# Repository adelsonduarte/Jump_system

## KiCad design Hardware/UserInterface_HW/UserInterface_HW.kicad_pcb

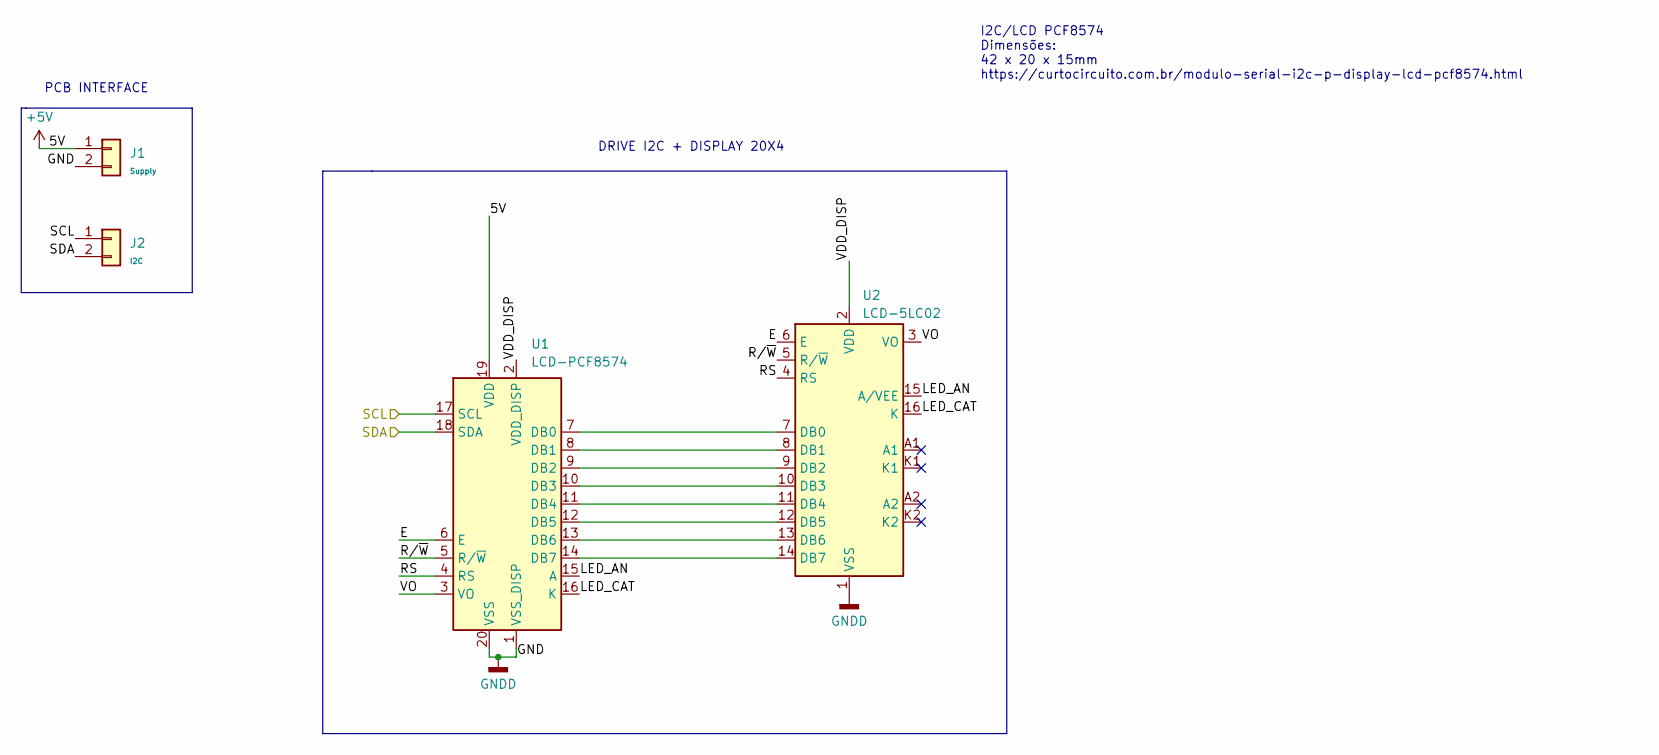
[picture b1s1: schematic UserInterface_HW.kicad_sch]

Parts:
J1: Supply; PinHeader_1x02_P2.54mm_Vertical
J2: I2C; PinHeader_1x02_P2.54mm_Vertical
U1: LCD-PCF8574; Módulo I2C - PCF8574
U2: LCD-5LC02; PinHeader_1x16_P2.54mm_Vertical

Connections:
+5V: J1.1, U1.19 (VDD)
/E: U1.6 (E), U2.6 (E)
/LED_AN: U1.15 (A), U2.15 (A/VEE)
/LED_CAT: U1.16 (K), U2.16 (K)
/RS: U1.4 (RS), U2.4 (RS)
/R/~W: U1.5 (R/~W), U2.5 (R/~W)
/SCL: J2.1, U1.17 (SCL)
/SDA: J2.2, U1.18 (SDA)
/VDD_DISP: U1.2 (VDD_DISP), U2.2 (VDD)
/VO: U1.3 (VO), U2.3 (VO)
GNDD: J1.2, U1.1 (VSS_DISP), U1.20 (VSS), U2.1 (VSS)
unnamed: U1.7 (DB0), U2.7 (DB0)
unnamed: U1.8 (DB1), U2.8 (DB1)
unnamed: U1.9 (DB2), U2.9 (DB2)
unnamed: U1.10 (DB3), U2.10 (DB3)
unnamed: U1.11 (DB4), U2.11 (DB4)
unnamed: U1.12 (DB5), U2.12 (DB5)
unnamed: U1.13 (DB6), U2.13 (DB6)
unnamed: U1.14 (DB7), U2.14 (DB7)

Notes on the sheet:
DRIVE I2C + DISPLAY 20X4
I2C/LCD PCF8574 Dimensões: 42 x 20 x 15mm https://curtocircuito.com.br/modulo-serial-i2c-p-display-lcd-pcf8574.html
PCB INTERFACE

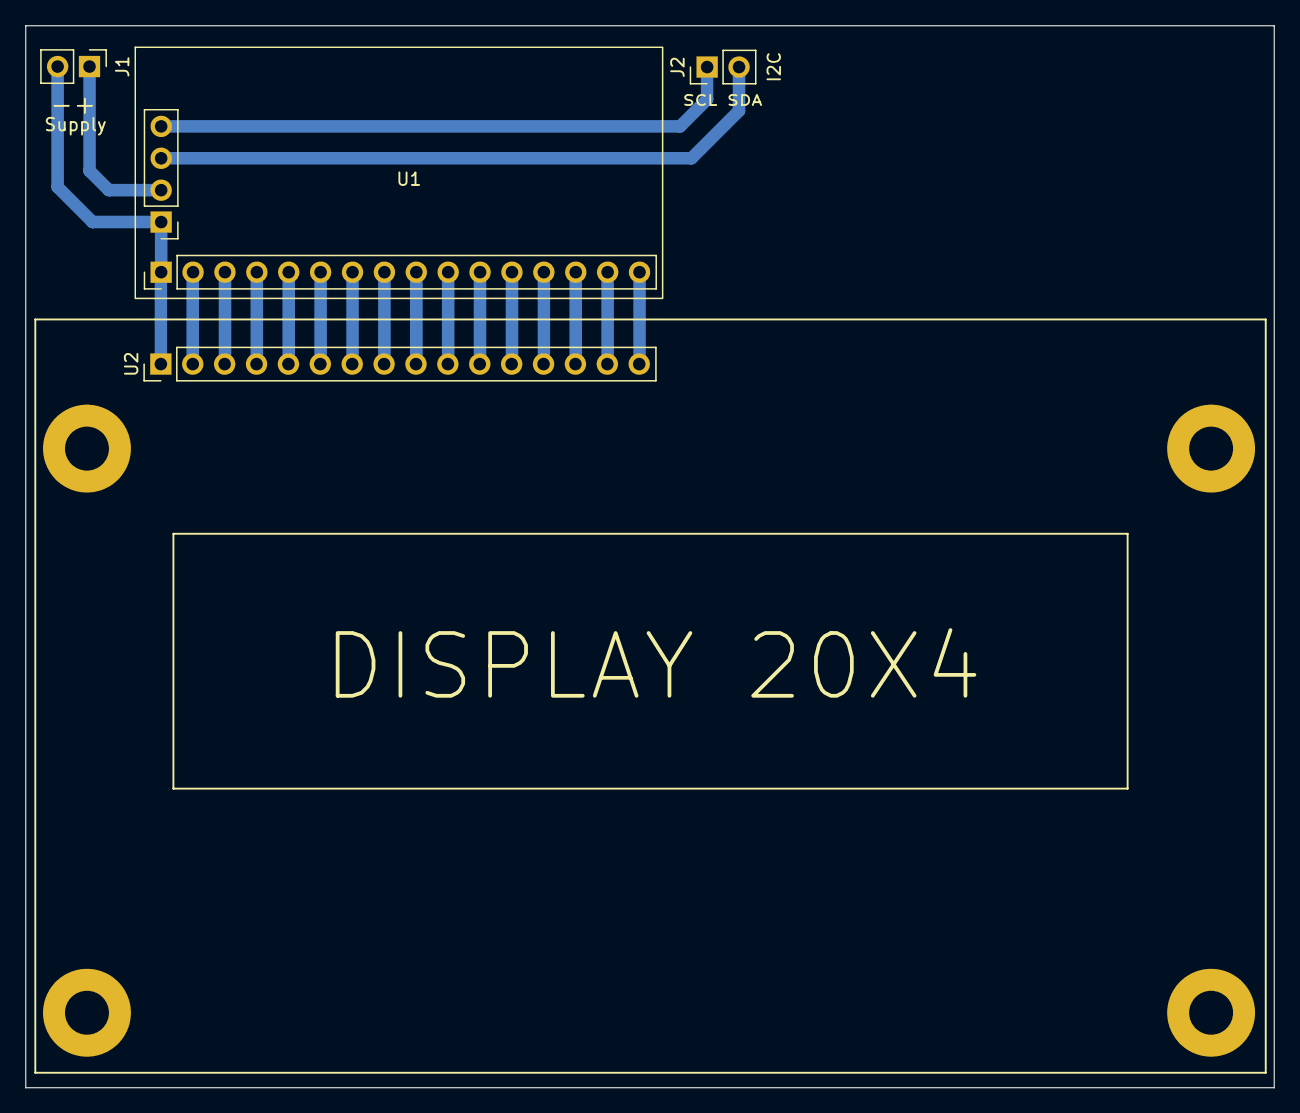
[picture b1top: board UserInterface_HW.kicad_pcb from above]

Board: 2 copper layers, 99.4 x 84.6 mm, 4 parts (0 on the bottom side), 19 nets.

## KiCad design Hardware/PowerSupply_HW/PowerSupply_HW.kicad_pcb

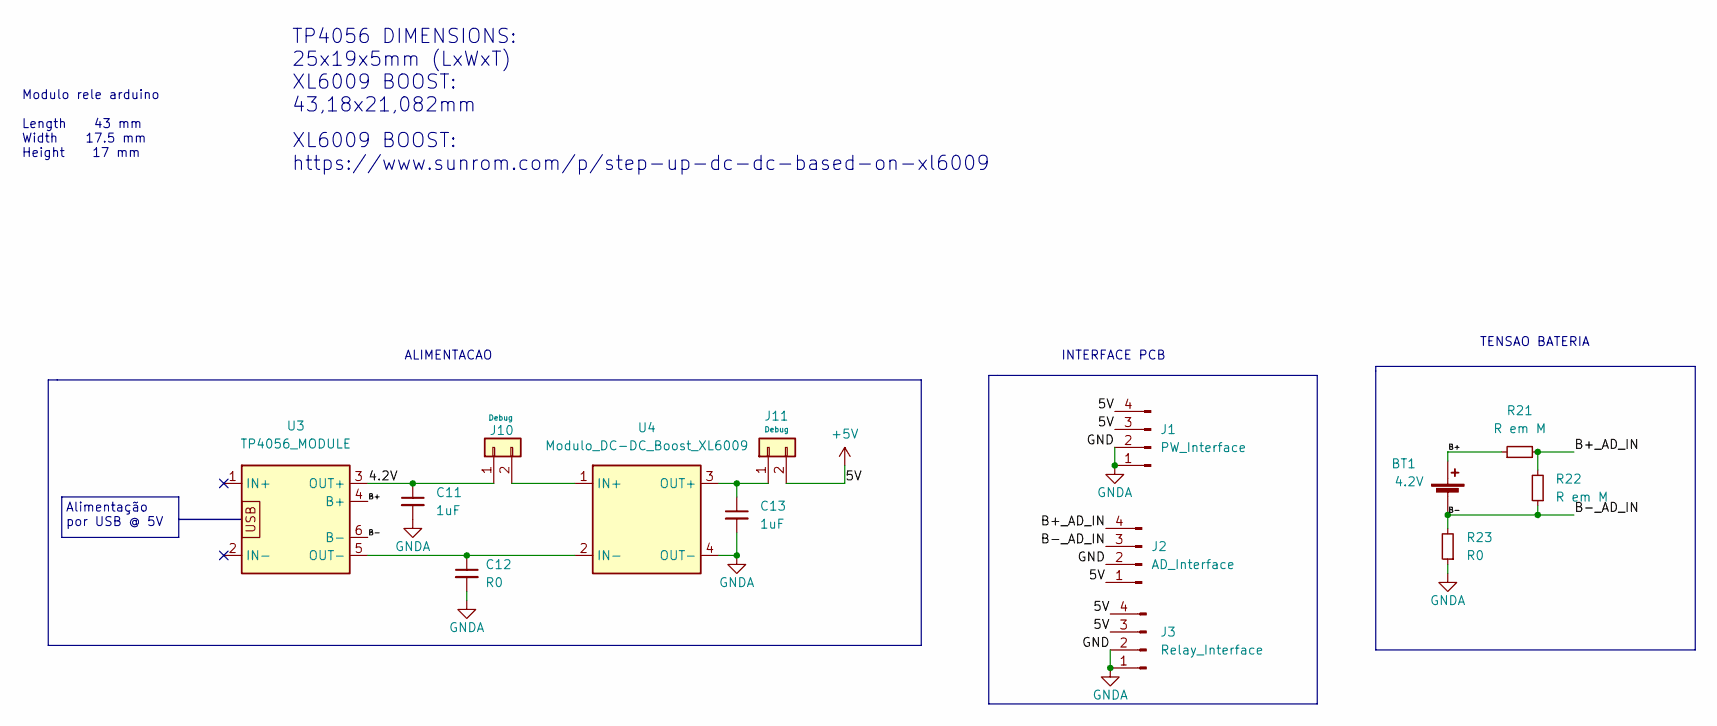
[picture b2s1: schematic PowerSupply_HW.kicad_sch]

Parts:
BT1: 4.2V; PinHeader_1x02_P2.54mm_Vertical
C11, C13: 1uF; C_0805_2012Metric
C12: R0; C_0805_2012Metric
J1: PW_Interface; PinHeader_1x04_P2.54mm_Vertical
J2: AD_Interface; PinHeader_1x04_P2.54mm_Vertical
J3: Relay_Interface; PinHeader_1x04_P2.54mm_Vertical
J10, J11: Debug; PinHeader_1x02_P2.54mm_Vertical
R21, R22: R em M; R_0805_2012Metric_Pad1.20x1.40mm_HandSolder
R23: R0; R_0805_2012Metric_Pad1.20x1.40mm_HandSolder
U3: TP4056_MODULE; Módulo_TP4056
U4: Modulo_DC-DC_Boost_XL6009

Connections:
+5V: J1.3, J1.4, J2.1, J3.3, J3.4, J11.2
/4.2V: C11.1, J10.1, U3.3 (OUT+)
/B+: BT1.1 (+), R21.1, U3.4 (B+); also elsewhere on the board
/B+_AD_IN: J2.4, R21.2, R22.2
/B-: BT1.2 (-), J2.3, R22.1, R23.2, U3.6 (B-); also elsewhere on the board
GNDA: C11.2, C12.2, C13.2, J1.1, J1.2, J2.2, J3.1, J3.2, R23.1, U4.4 (OUT-)
unnamed: C12.1, U3.5 (OUT-), U4.2 (IN-)
unnamed: C13.1, J11.1, U4.3 (OUT+)
unnamed: J10.2, U4.1 (IN+)

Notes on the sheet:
XL6009 BOOST: https://www.sunrom.com/p/step-up-dc-dc-based-on-xl6009
TENSAO BATERIA
Modulo rele arduino Length 43 mm Width 17.5 mm Height 17 mm
INTERFACE PCB
Alimentação por USB @ 5V
TP4056 DIMENSIONS: 25x19x5mm (LxWxT) XL6009 BOOST: 43,18x21,082mm
ALIMENTACAO

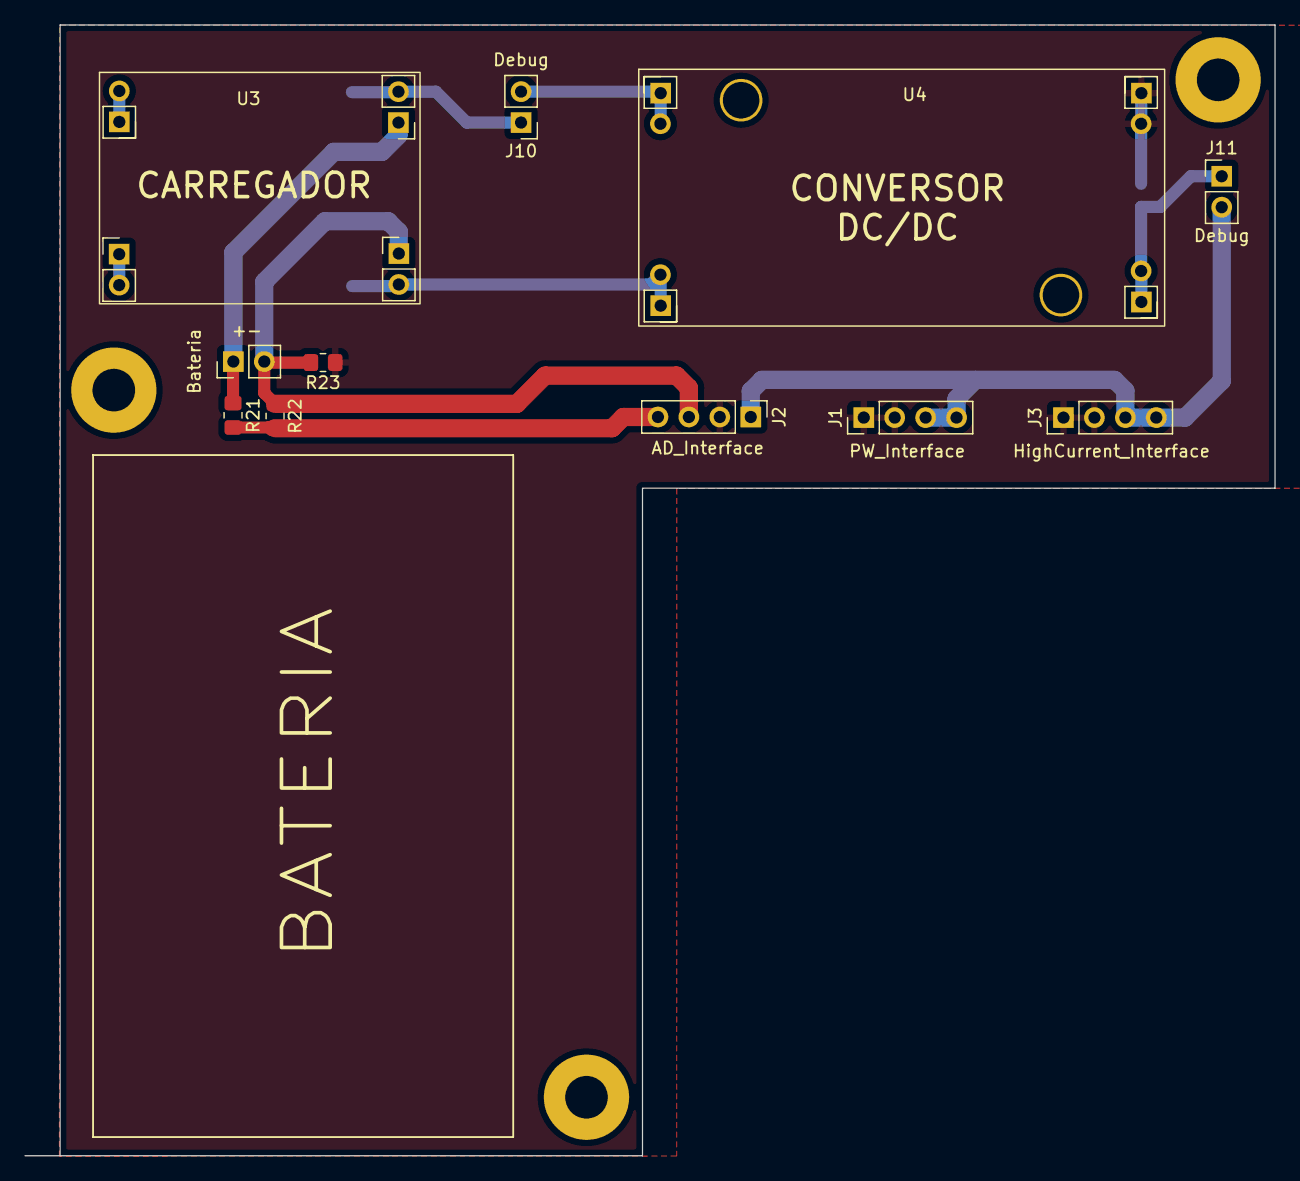
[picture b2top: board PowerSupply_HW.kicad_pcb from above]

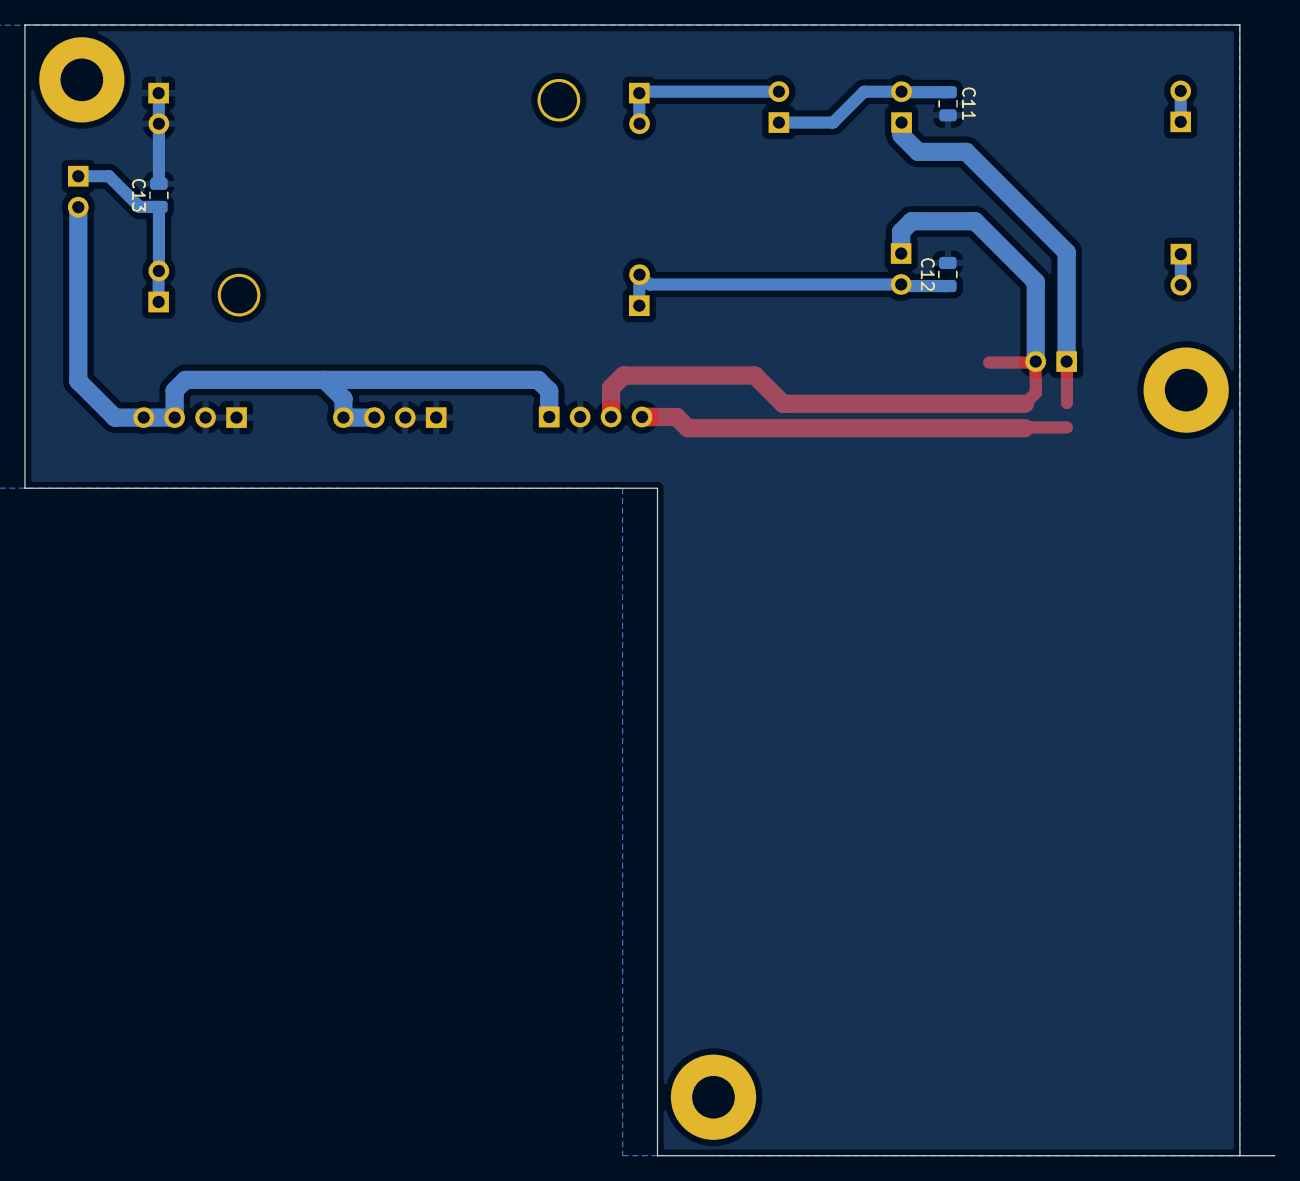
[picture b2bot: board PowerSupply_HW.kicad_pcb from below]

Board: 2 copper layers, 102.6 x 92.9 mm, 14 parts (3 on the bottom side), 9 nets.

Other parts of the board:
Bateria: 4.2V; PinHeader_1x02_P2.54mm_Vertical

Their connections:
/B+: Bateria.1 (+); also elsewhere on the board
/B-: Bateria.2 (-); also elsewhere on the board

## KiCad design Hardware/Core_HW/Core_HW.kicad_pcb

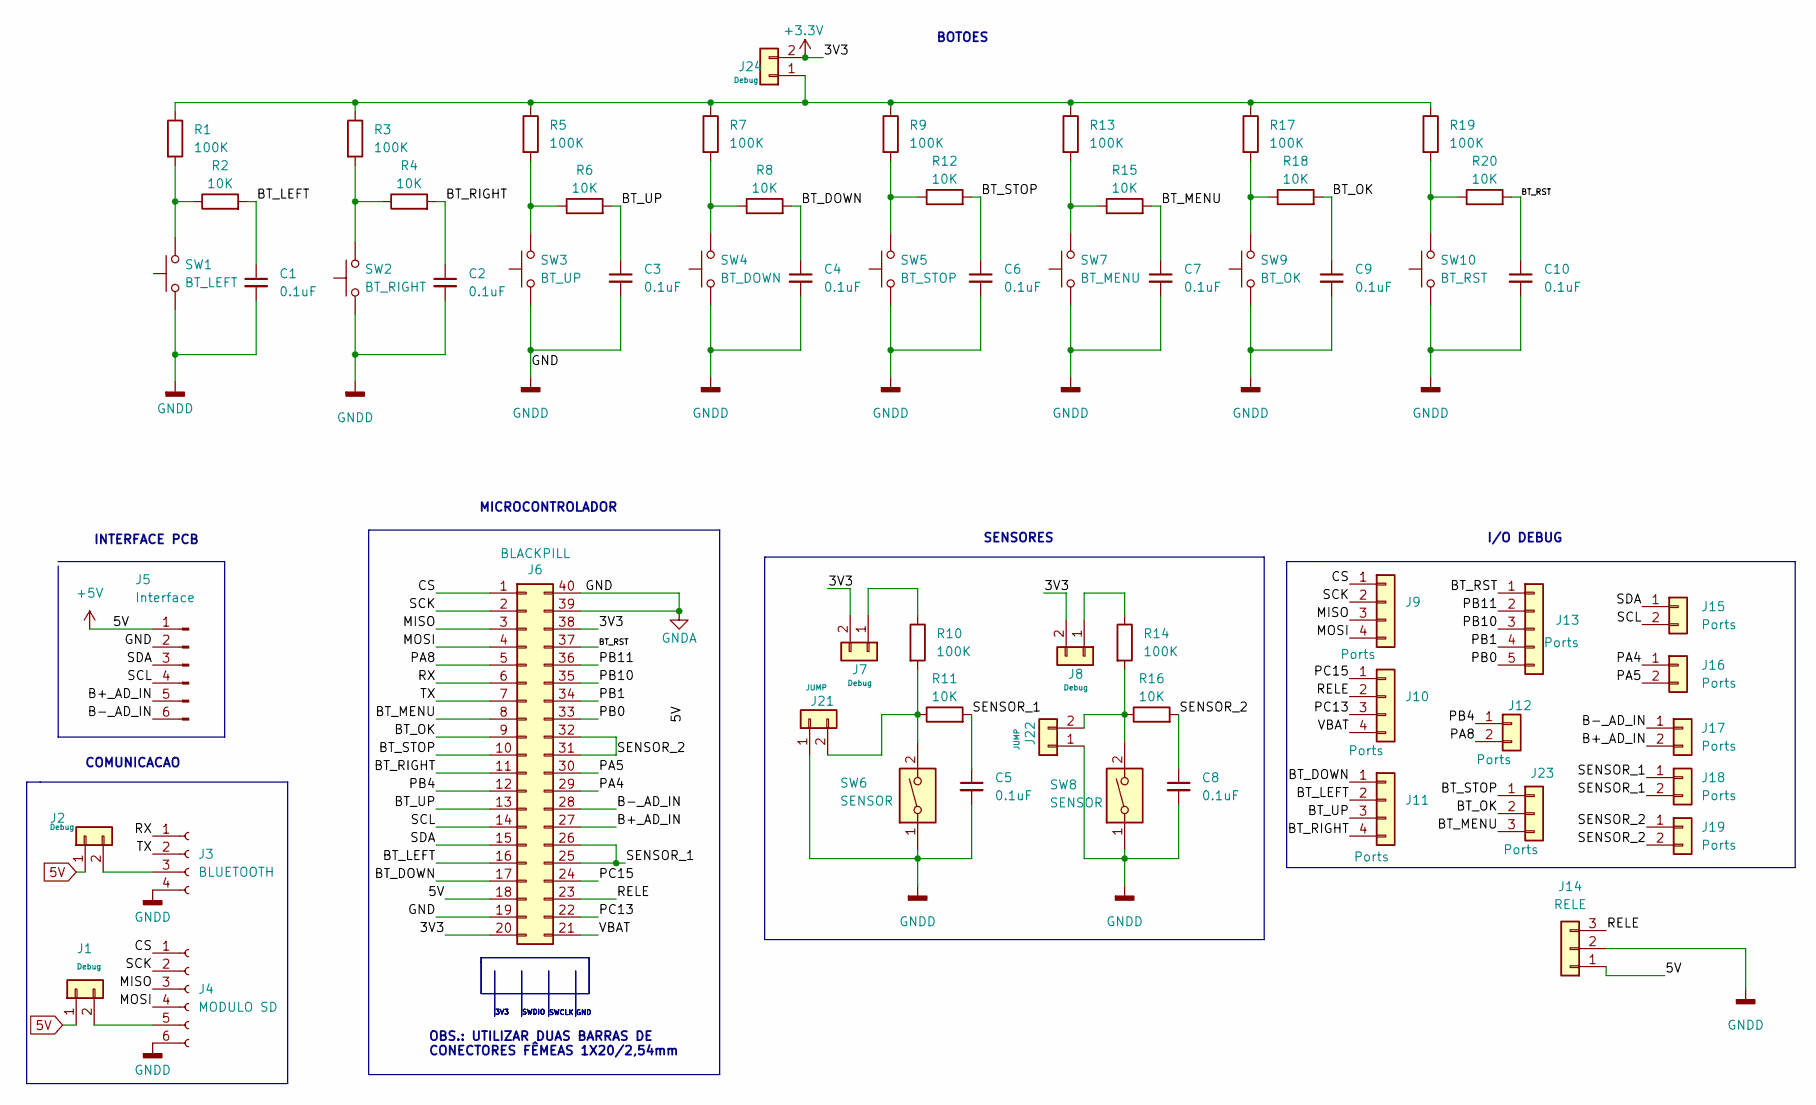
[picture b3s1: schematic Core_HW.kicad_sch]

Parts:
C1, C2, C3, C4, C5, C6, C7, C8, C9, C10: 0.1uF; R_0805_2012Metric_Pad1.20x1.40mm_HandSolder
J1, J2, J7, J8, J24: Debug; PinHeader_1x02_P2.54mm_Vertical
J3: BLUETOOTH; PinHeader_1x04_P2.54mm_Vertical
J4: MODULO SD; PinHeader_1x06_P2.54mm_Vertical
J5: Interface; PinHeader_1x06_P2.54mm_Vertical
J6: BLACKPILL; DIP-40_W15.24mm_Socket_LongPads
J9, J10, J11: Ports; PinHeader_1x04_P2.54mm_Vertical
J12, J15, J16, J17, J18, J19: Ports; PinHeader_1x02_P2.54mm_Vertical
J13: Ports; PinHeader_1x05_P2.54mm_Vertical
J14: RELE; PinHeader_1x03_P2.54mm_Vertical
J21, J22: JUMP; PinHeader_1x02_P2.54mm_Vertical
J23: Ports; PinHeader_1x03_P2.54mm_Vertical
R1, R3, R5, R7, R9, R10, R13, R14, R17, R19: 100K; R_0805_2012Metric_Pad1.20x1.40mm_HandSolder
R2, R4, R6, R8, R11, R12, R15, R16, R18, R20: 10K; R_0805_2012Metric_Pad1.20x1.40mm_HandSolder
SW1: BT_LEFT; SW_PUSH_6mm
SW2: BT_RIGHT; SW_PUSH_6mm
SW3: BT_UP; SW_PUSH_6mm
SW4: BT_DOWN; SW_PUSH_6mm
SW5: BT_STOP; SW_PUSH_6mm
SW6, SW8: SENSOR; Molex_KK-254_AE-6410-02A_1x02_P2.54mm_Vertical
SW7: BT_MENU; SW_PUSH_6mm
SW9: BT_OK; SW_PUSH_6mm
SW10: BT_RST; SW_PUSH_6mm

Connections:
5V: J1.1, J2.1, J5.1, J6.18, J14.1
+3.3V: J6.20, J6.38, J7.2, J8.2, J24.2
/B+_AD_IN: J5.5, J6.27, J17.2
/B-_AD_IN: J5.6, J6.28, J17.1
/BT_DOWN: C4.1, J6.17, J11.1, R8.2
/BT_LEFT: C1.1, J6.16, J11.2, R2.2
/BT_MENU: C7.1, J6.8, J23.3, R15.2
/BT_OK: C9.1, J6.9, J23.2, R18.2
/BT_RIGHT: C2.1, J6.11, J11.4, R4.2
/BT_RST: C10.1, J6.37, J13.1, R20.2
/BT_STOP: C6.1, J6.10, J23.1, R12.2
/BT_UP: C3.1, J6.13, J11.3, R6.2
/CS: J4.1, J6.1, J9.1
/MISO: J4.3, J6.3, J9.3
/MOSI: J4.4, J6.4, J9.4
/PA4: J6.29, J16.1
/PA5: J6.30, J16.2
/PA8: J6.5, J12.2
/PB0: J6.33, J13.5
/PB1: J6.34, J13.4
/PB4: J6.12, J12.1
/PB10: J6.35, J13.3
/PB11: J6.36, J13.2
/PC13: J6.22, J10.3
/PC15: J6.24, J10.1
/RELE: J6.23, J10.2, J14.3
/RX: J3.1, J6.6
/SCK: J4.2, J6.2, J9.2
/SCL: J5.4, J6.14, J15.2
/SDA: J5.3, J6.15, J15.1
/SENSOR_1: C5.1, J6.25, J6.26, J18.1, J18.2, R11.2
/SENSOR_2: C8.1, J6.31, J6.32, J19.1, J19.2, R16.2
/TX: J3.2, J6.7
/VBAT: J6.21, J10.4
GNDA: C1.2, C2.2, C3.2, C4.2, C5.2, C6.2, C7.2, C8.2, C9.2, C10.2, J3.4, J4.6, J5.2, J6.19, J6.39, J6.40, J14.2, J21.1, J22.1, SW1.1, SW2.1, SW3.1, SW4.1, SW5.1, SW6.1, SW7.1, SW8.1, SW9.1, SW10.1
unnamed: J1.2, J4.5
unnamed: J2.2, J3.3
unnamed: J7.1, R10.1
unnamed: J8.1, R14.1
unnamed: J21.2, R10.2, R11.1, SW6.2
unnamed: J22.2, R14.2, R16.1, SW8.2
unnamed: J24.1, R1.1, R3.1, R5.1, R7.1, R9.1, R13.1, R17.1, R19.1
unnamed: R1.2, R2.1, SW1.2
unnamed: R3.2, R4.1, SW2.2
unnamed: R5.2, R6.1, SW3.2
unnamed: R7.2, R8.1, SW4.2
unnamed: R9.2, R12.1, SW5.2
unnamed: R13.2, R15.1, SW7.2
unnamed: R17.2, R18.1, SW9.2
unnamed: R19.2, R20.1, SW10.2

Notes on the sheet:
SWCLK
I/O DEBUG
GND
SWDIO
3V3
INTERFACE PCB
COMUNICACAO
BOTOES
SENSORES
MICROCONTROLADOR
OBS.: UTILIZAR DUAS BARRAS DE CONECTORES FÊMEAS 1X20/2,54mm

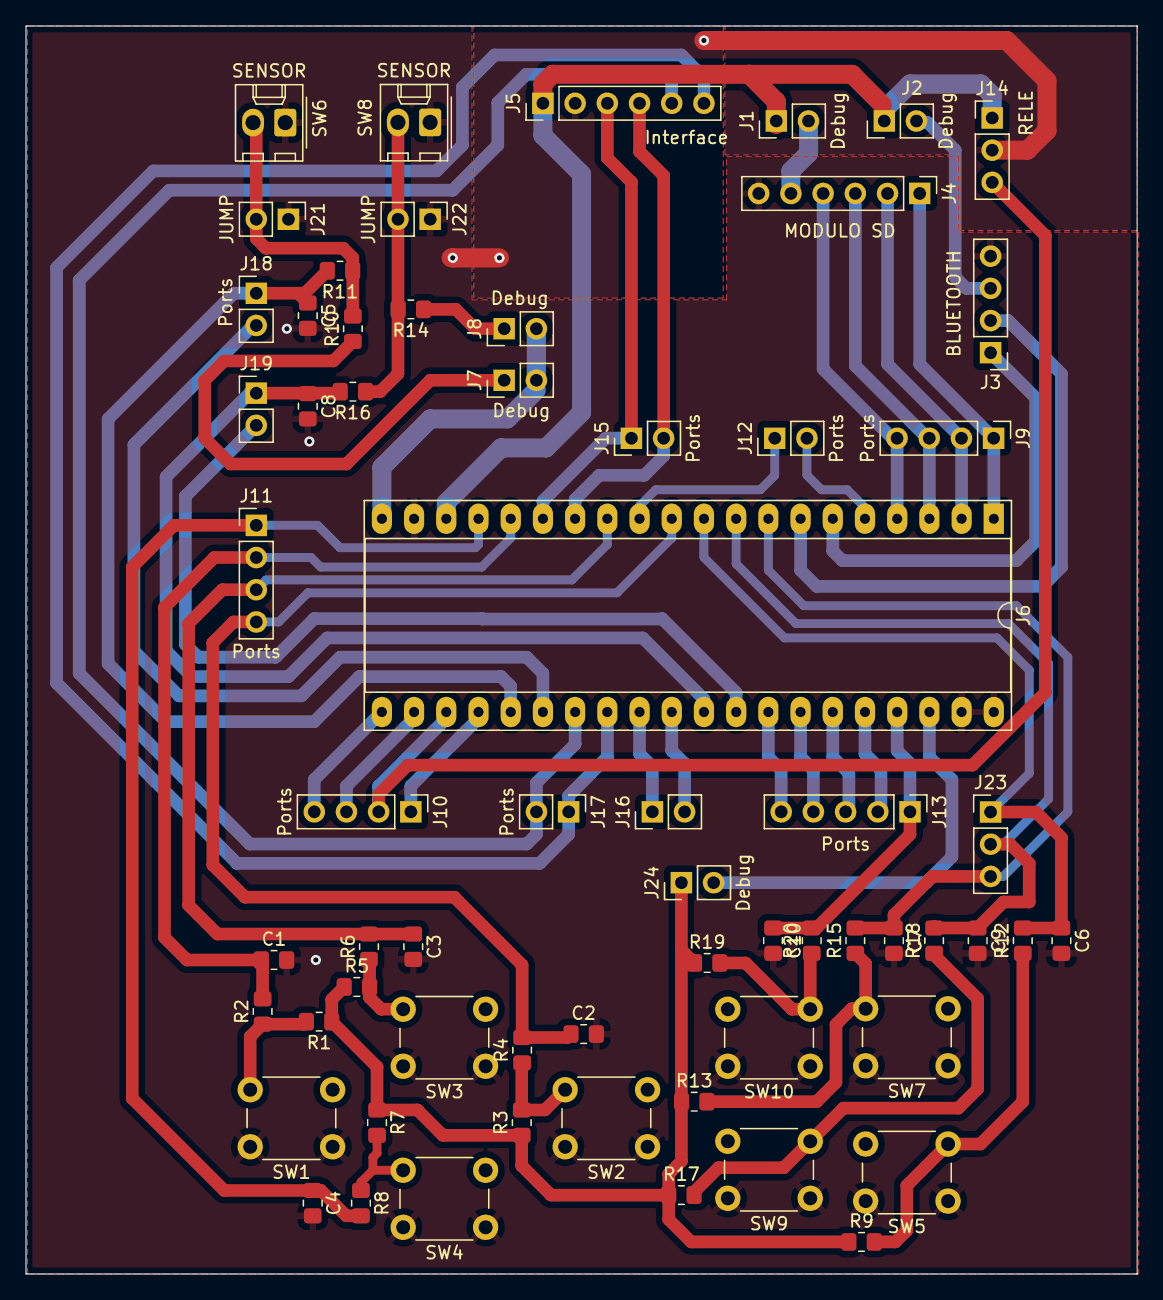
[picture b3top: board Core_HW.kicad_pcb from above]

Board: 2 copper layers, 87.6 x 98.4 mm, 63 parts (0 on the bottom side), 50 nets.

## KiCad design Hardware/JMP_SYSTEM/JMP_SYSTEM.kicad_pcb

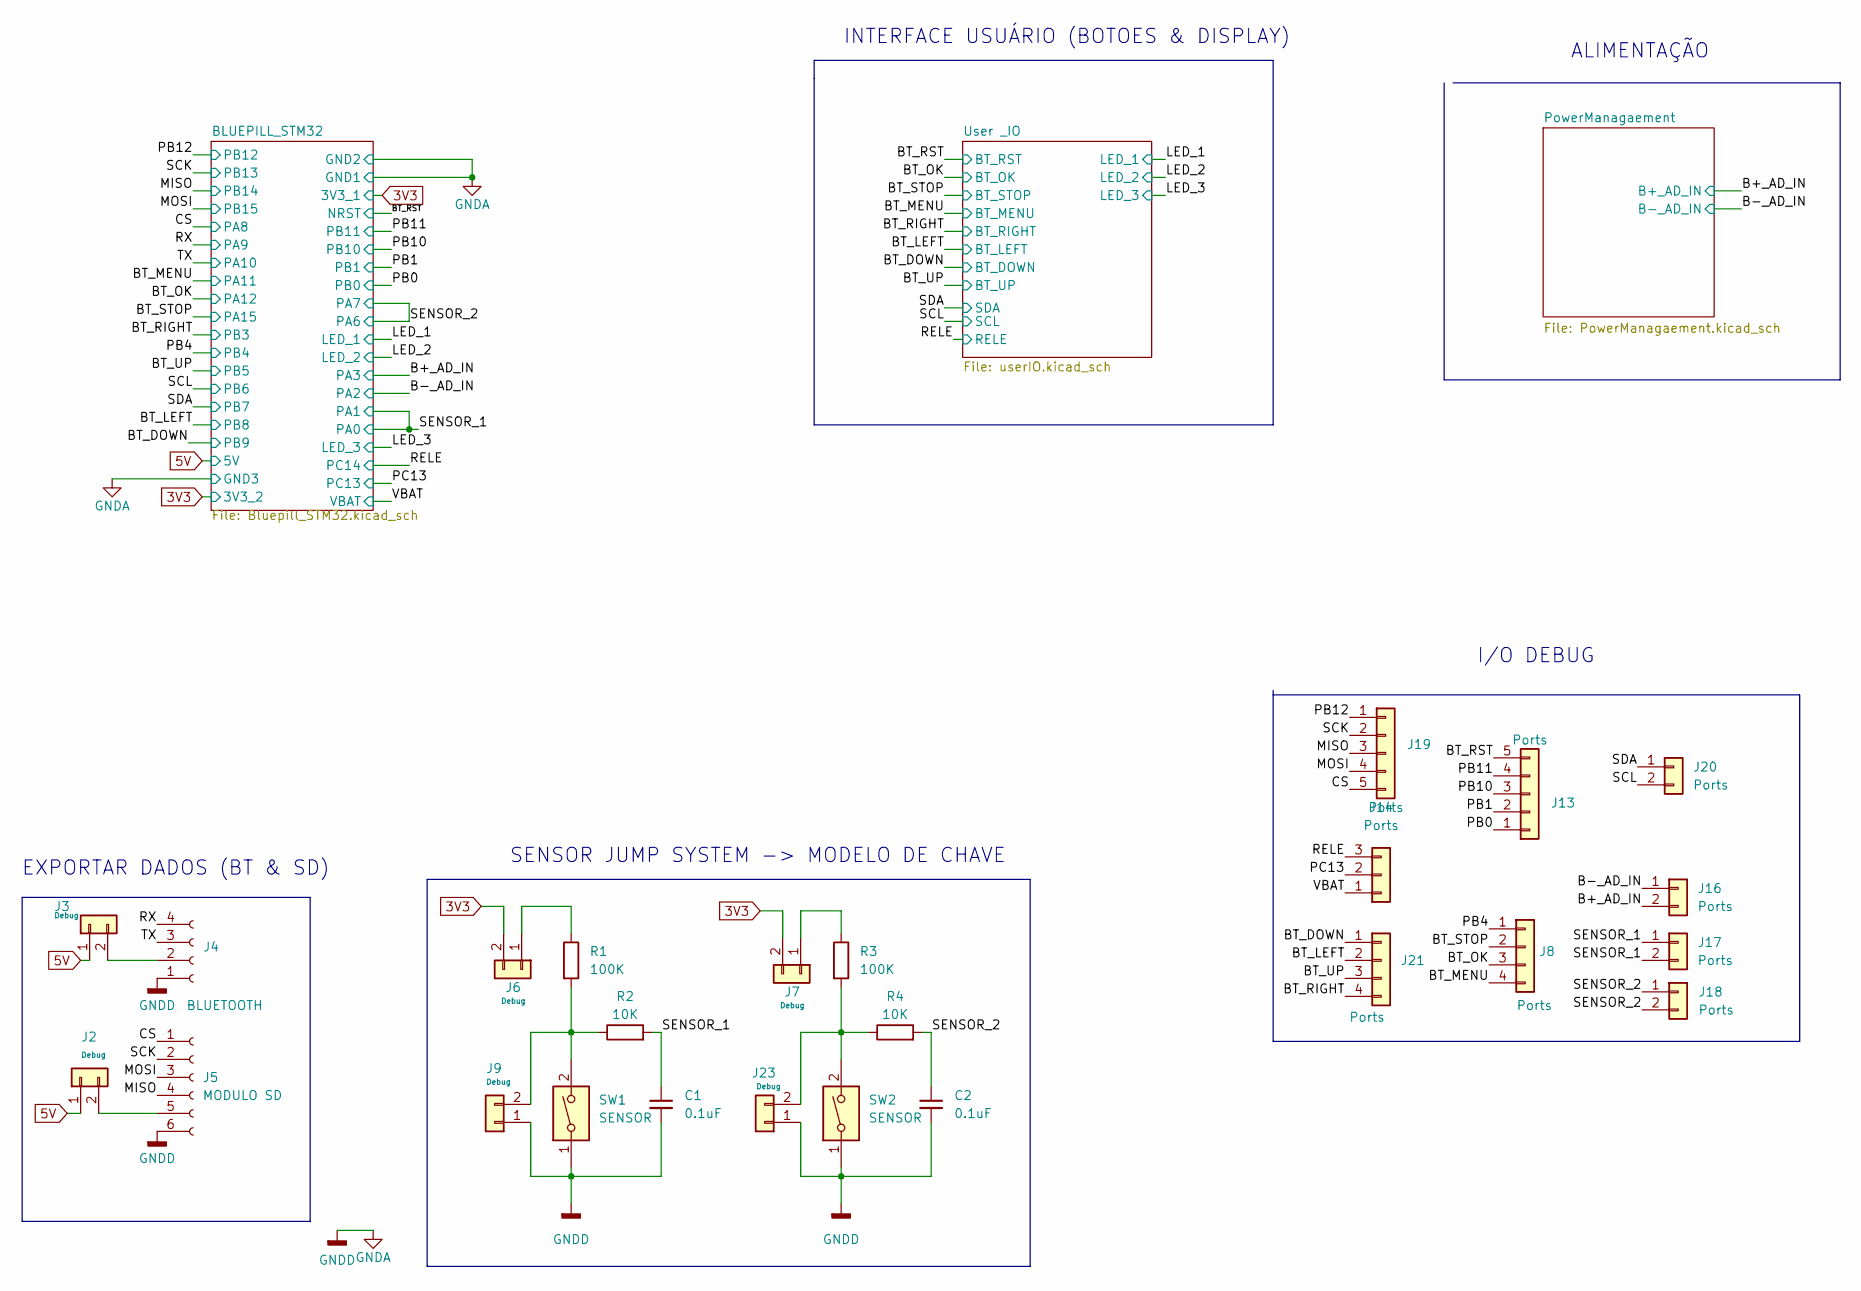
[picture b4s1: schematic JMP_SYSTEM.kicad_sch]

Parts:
C1, C2: 0.1uF; R_0805_2012Metric_Pad1.20x1.40mm_HandSolder
J2, J3, J6, J7, J9, J23: Debug; PinHeader_1x02_P2.54mm_Vertical
J4: BLUETOOTH; Molex_KK-254_AE-6410-04A_1x04_P2.54mm_Vertical
J5: MODULO SD; Molex_KK-254_AE-6410-06A_1x06_P2.54mm_Vertical
J8, J21: Ports; Molex_KK-254_AE-6410-04A_1x04_P2.54mm_Vertical
J13, J19: Ports; Molex_KK-254_AE-6410-05A_1x05_P2.54mm_Vertical
J14: Ports; Molex_KK-254_AE-6410-03A_1x03_P2.54mm_Vertical
J16, J17, J18, J20: Ports; Molex_KK-254_AE-6410-02A_1x02_P2.54mm_Vertical
R1, R3: 100K; R_0805_2012Metric_Pad1.20x1.40mm_HandSolder
R2, R4: 10K; R_0805_2012Metric_Pad1.20x1.40mm_HandSolder
SW1, SW2: SENSOR; Molex_KK-254_AE-6410-02A_1x02_P2.54mm_Vertical

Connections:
3V3: J6.2, J7.2; also elsewhere on the board
5V: J2.1, J3.1; also elsewhere on the board
/B+_AD_IN: J16.2; also elsewhere on the board
/B-_AD_IN: J16.1; also elsewhere on the board
/BT_DOWN: J21.1; also elsewhere on the board
/BT_LEFT: J21.2; also elsewhere on the board
/BT_MENU: J8.4; also elsewhere on the board
/BT_OK: J8.3; also elsewhere on the board
/BT_RIGHT: J21.4; also elsewhere on the board
/BT_RST: J13.5; also elsewhere on the board
/BT_STOP: J8.2; also elsewhere on the board
/BT_UP: J21.3; also elsewhere on the board
/CS: J5.1, J19.5; also elsewhere on the board
/MISO: J5.4, J19.3; also elsewhere on the board
/MOSI: J5.3, J19.4; also elsewhere on the board
/PB0: J13.1; also elsewhere on the board
/PB1: J13.2; also elsewhere on the board
/PB4: J8.1; also elsewhere on the board
/PB10: J13.3; also elsewhere on the board
/PB11: J13.4; also elsewhere on the board
/PB12: J19.1; also elsewhere on the board
/PC13: J14.2; also elsewhere on the board
/RELE: J14.3; also elsewhere on the board
/RX: J4.4; also elsewhere on the board
/SCK: J5.2, J19.2; also elsewhere on the board
/SCL: J20.2; also elsewhere on the board
/SDA: J20.1; also elsewhere on the board
/SENSOR_1: C1.1, J17.1, J17.2, R2.2; also elsewhere on the board
/SENSOR_2: C2.1, J18.1, J18.2, R4.2; also elsewhere on the board
/TX: J4.3; also elsewhere on the board
/VBAT: J14.1; also elsewhere on the board
GNDA: C1.2, C2.2, J4.1, J5.6, J9.1, J23.1, SW1.1, SW2.1; also elsewhere on the board
unnamed: J2.2, J5.5
unnamed: J3.2, J4.2
unnamed: J6.1, R1.1
unnamed: J7.1, R3.1
unnamed: J9.2, R1.2, R2.1, SW1.2
unnamed: J23.2, R3.2, R4.1, SW2.2

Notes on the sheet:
INTERFACE USUÁRIO (BOTOES & DISPLAY)
ALIMENTAÇÃO
EXPORTAR DADOS (BT & SD)
SENSOR JUMP SYSTEM -> MODELO DE CHAVE
I/O DEBUG

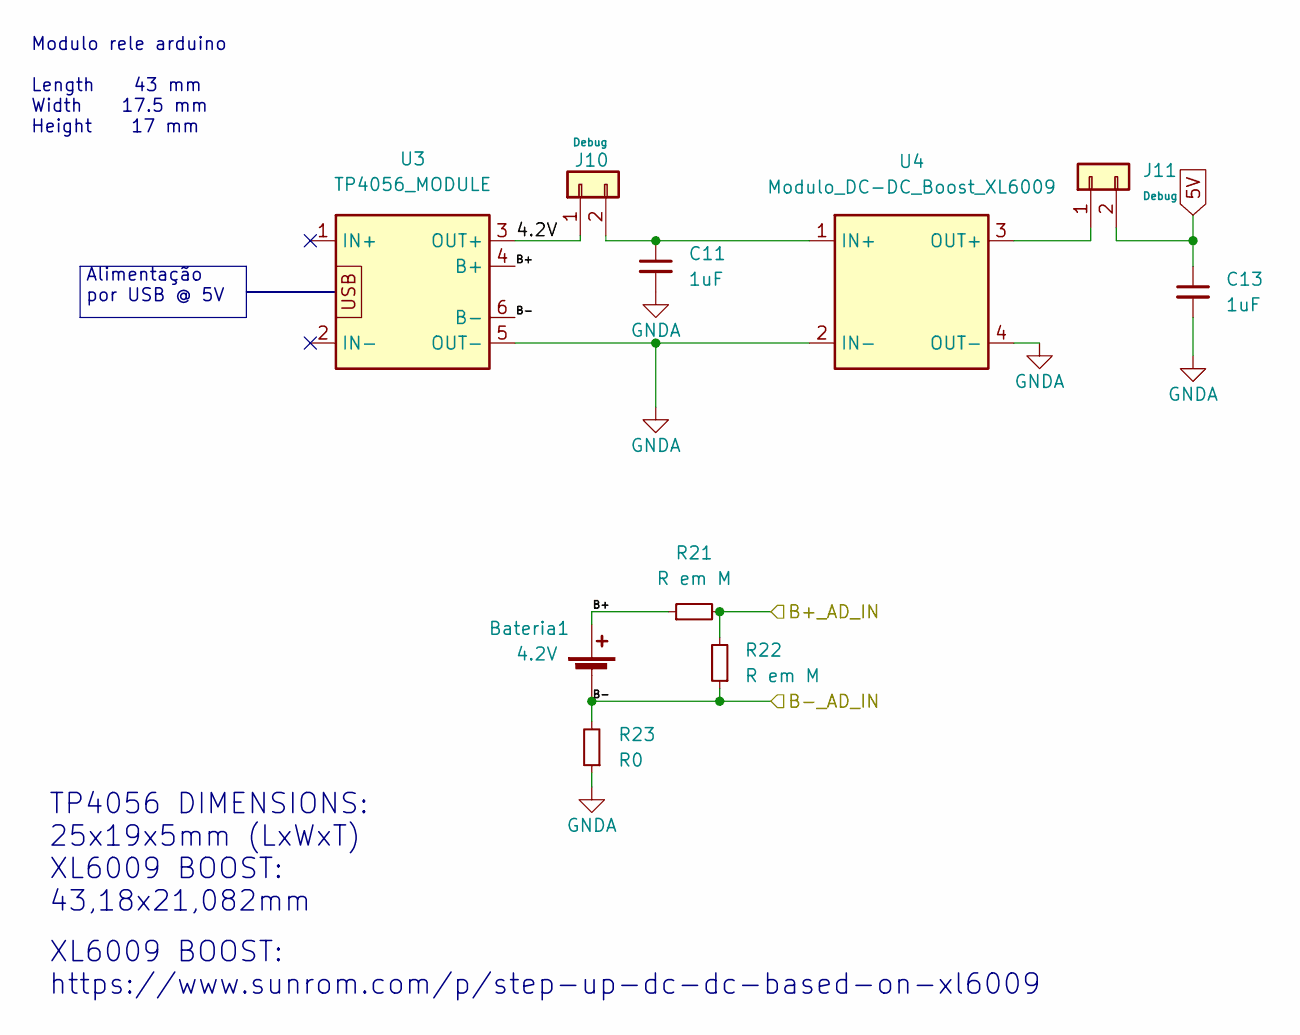
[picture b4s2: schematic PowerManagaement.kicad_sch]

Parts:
Bateria1: 4.2V; Molex_KK-254_AE-6410-02A_1x02_P2.54mm_Vertical
C11, C13: 1uF; C_0805_2012Metric
J10, J11: Debug; PinHeader_1x02_P2.54mm_Vertical
R21, R22: R em M; R_0805_2012Metric_Pad1.20x1.40mm_HandSolder
R23: R0; R_0805_2012Metric_Pad1.20x1.40mm_HandSolder
U3: TP4056_MODULE; Módulo_TP4056
U4: Modulo_DC-DC_Boost_XL6009

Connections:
5V: C13.1, J11.2; also elsewhere on the board
/B+_AD_IN: R21.2, R22.2; also elsewhere on the board
/B-_AD_IN: Bateria1.2 (-), R22.1, R23.2, U3.6 (B-); also elsewhere on the board
/PowerManagaement/4.2V: J10.1, U3.3 (OUT+)
/PowerManagaement/B+: Bateria1.1 (+), R21.1, U3.4 (B+)
GNDA: C11.2, C13.2, R23.1, U3.5 (OUT-), U4.2 (IN-), U4.4 (OUT-); also elsewhere on the board
unnamed: C11.1, J10.2, U4.1 (IN+)
unnamed: J11.1, U4.3 (OUT+)

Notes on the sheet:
XL6009 BOOST: https://www.sunrom.com/p/step-up-dc-dc-based-on-xl6009
Modulo rele arduino Length 43 mm Width 17.5 mm Height 17 mm
Alimentação por USB @ 5V
TP4056 DIMENSIONS: 25x19x5mm (LxWxT) XL6009 BOOST: 43,18x21,082mm

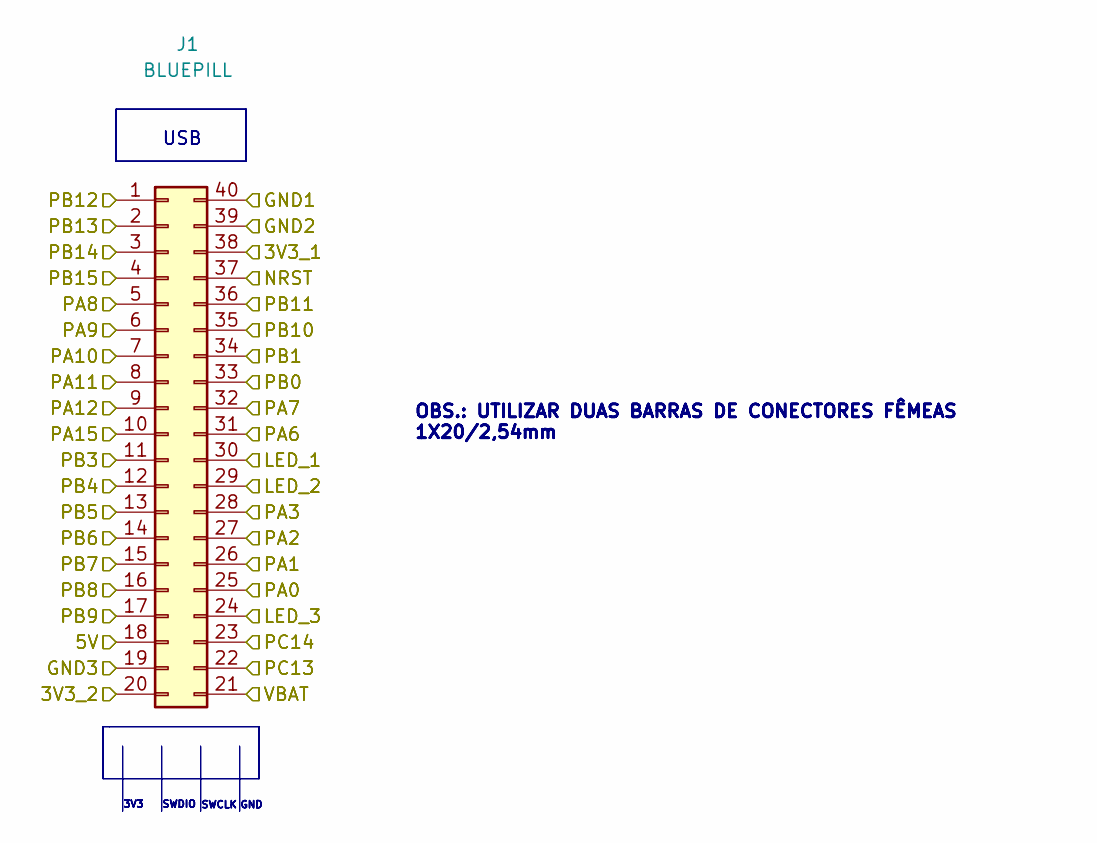
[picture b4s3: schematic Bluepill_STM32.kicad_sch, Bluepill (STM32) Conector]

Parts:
J1: BLUEPILL; DIP-40_W15.24mm_Socket_LongPads

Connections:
3V3: J1.20, J1.38; also elsewhere on the board
5V: J1.18; also elsewhere on the board
/B+_AD_IN: J1.28; also elsewhere on the board
/B-_AD_IN: J1.27; also elsewhere on the board
/BT_DOWN: J1.17; also elsewhere on the board
/BT_LEFT: J1.16; also elsewhere on the board
/BT_MENU: J1.8; also elsewhere on the board
/BT_OK: J1.9; also elsewhere on the board
/BT_RIGHT: J1.11; also elsewhere on the board
/BT_RST: J1.37; also elsewhere on the board
/BT_STOP: J1.10; also elsewhere on the board
/BT_UP: J1.13; also elsewhere on the board
/CS: J1.5; also elsewhere on the board
/LED_1: J1.30; also elsewhere on the board
/LED_2: J1.29; also elsewhere on the board
/LED_3: J1.24; also elsewhere on the board
/MISO: J1.3; also elsewhere on the board
/MOSI: J1.4; also elsewhere on the board
/PB0: J1.33; also elsewhere on the board
/PB1: J1.34; also elsewhere on the board
/PB4: J1.12; also elsewhere on the board
/PB10: J1.35; also elsewhere on the board
/PB11: J1.36; also elsewhere on the board
/PB12: J1.1; also elsewhere on the board
/PC13: J1.22; also elsewhere on the board
/RELE: J1.23; also elsewhere on the board
/RX: J1.6; also elsewhere on the board
/SCK: J1.2; also elsewhere on the board
/SCL: J1.14; also elsewhere on the board
/SDA: J1.15; also elsewhere on the board
/SENSOR_1: J1.25, J1.26; also elsewhere on the board
/SENSOR_2: J1.31, J1.32; also elsewhere on the board
/TX: J1.7; also elsewhere on the board
/VBAT: J1.21; also elsewhere on the board
GNDA: J1.19, J1.39, J1.40; also elsewhere on the board

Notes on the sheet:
USB
SWCLK
SWDIO
GND
OBS.: UTILIZAR DUAS BARRAS DE CONECTORES FÊMEAS 1X20/2,54mm
3V3
